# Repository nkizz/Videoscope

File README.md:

Board for viewing composite video (PAL, NTSC, or SECAM) on an oscilliscope
This is a layout of [this circuit by W2AEW](https://www.youtube.com/watch?v=yf4kOMSPbM0)

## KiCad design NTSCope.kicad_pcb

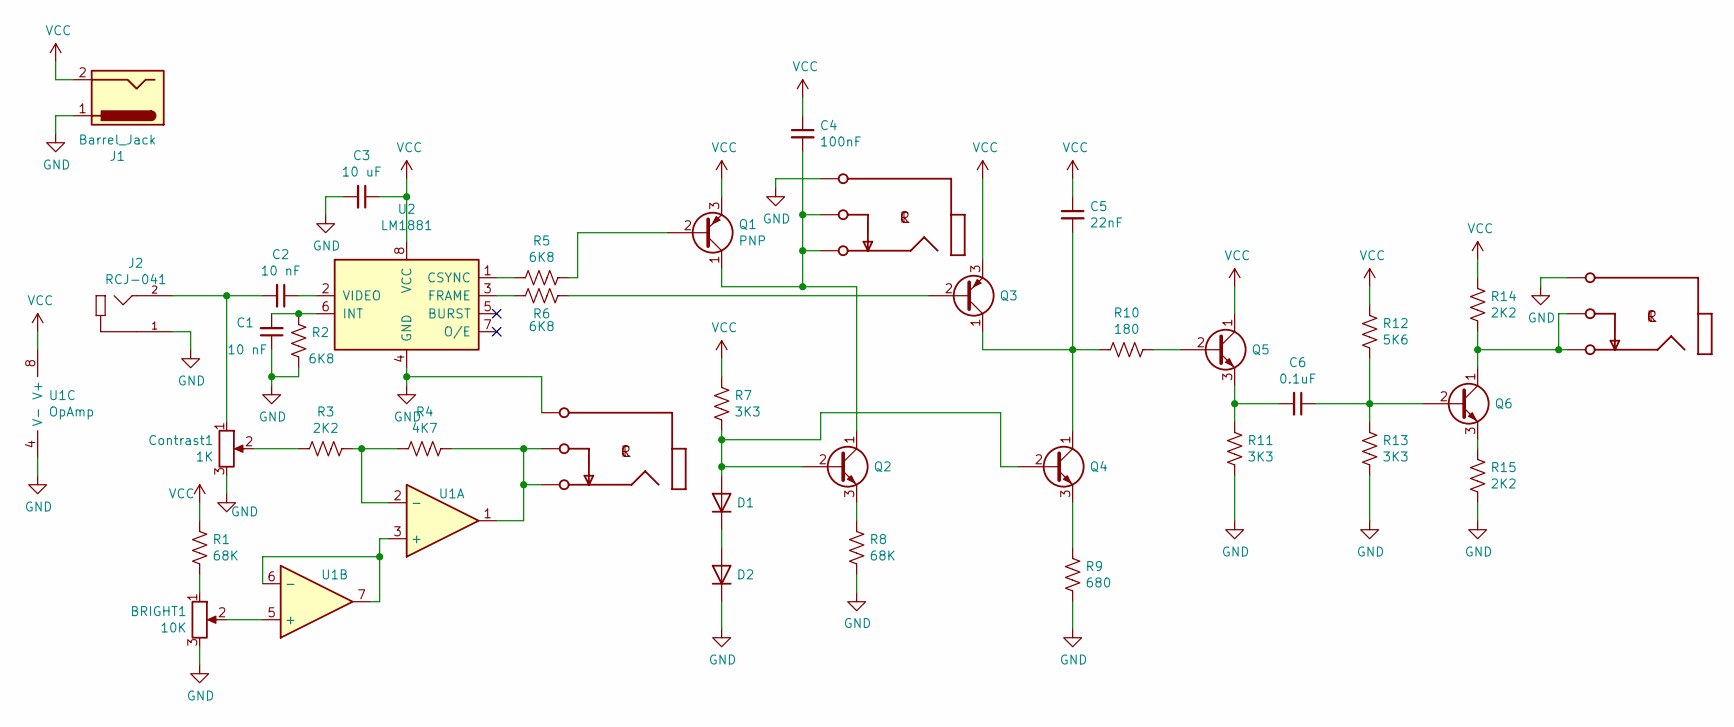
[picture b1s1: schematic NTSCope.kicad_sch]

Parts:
BRIGHT1: 10K; Potentiometer_Vishay_T73YP_Vertical
C1, C2: 10 nF; C_Disc_D5.0mm_W2.5mm_P2.50mm
C3: 10 uF; C_Disc_D5.0mm_W2.5mm_P2.50mm
C4: 100nF; C_Disc_D5.0mm_W2.5mm_P2.50mm
C5: 22nF; C_Disc_D5.0mm_W2.5mm_P2.50mm
C6: 0.1uF; C_Disc_D5.0mm_W2.5mm_P2.50mm
Contrast1: 1K; Potentiometer_Vishay_T73YP_Vertical
D1, D2: D; D_A-405_P7.62mm_Horizontal
J1: Barrel_Jack; BarrelJack_CUI_PJ-063AH_Horizontal_CircularHoles
J2: RCJ-041; CUI_RCJ-041
J3: PJRAN3X1U03X; PJRAN3X1U01X
Q1, Q3: PNP; TO-92_Inline_Wide
Q2, Q4, Q5, Q6: NPN; TO-92_Inline_Wide
R1, R8: 68K; R_Axial_DIN0207_L6.3mm_D2.5mm_P10.16mm_Horizontal
R2, R5, R6: 6K8; R_Axial_DIN0207_L6.3mm_D2.5mm_P10.16mm_Horizontal
R3, R14, R15: 2K2; R_Axial_DIN0207_L6.3mm_D2.5mm_P10.16mm_Horizontal
R4: 4K7; R_Axial_DIN0207_L6.3mm_D2.5mm_P10.16mm_Horizontal
R7, R11, R13: 3K3; R_Axial_DIN0207_L6.3mm_D2.5mm_P10.16mm_Horizontal
R9: 680; R_Axial_DIN0207_L6.3mm_D2.5mm_P10.16mm_Horizontal
R10: 180; R_Axial_DIN0207_L6.3mm_D2.5mm_P10.16mm_Horizontal
R12: 5K6; R_Axial_DIN0207_L6.3mm_D2.5mm_P10.16mm_Horizontal
U1: OpAmp; DIP-8_W7.62mm
U2: LM1881; DIP-8_W7.62mm

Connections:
GND: BRIGHT1.3, C1.1, C3.2, Contrast1.3, D2.1 (K), J1.1, J2.1, J3.1, J3.4, J3.7, R2.1, R8.2, R9.2, R11.2, R13.2, R15.2, U1.4 (V-), U2.4 (GND); also elsewhere on the board
unnamed 1: BRIGHT1.2, U1.5 (+); also elsewhere on the board
unnamed: C1.2, R2.2, U2.6 (INT)
unnamed: C2.1, U2.2 (VIDEO)
unnamed 4: C2.2, Contrast1.1, J2.2; also elsewhere on the board
unnamed: C4.2, J3.5, J3.6, Q1.1 (C), Q2.1 (C)
unnamed: C5.2, Q3.1 (C), Q4.1 (C), R10.2
unnamed: C6.1, Q6.2 (B), R12.2, R13.1
unnamed: C6.2, Q5.3 (E), R11.1
unnamed 9: Contrast1.2, R3.2; also elsewhere on the board
unnamed: D1.1 (K), D2.2 (A)
unnamed: D1.2 (A), Q2.2 (B), Q4.2 (B), R7.2
unnamed: J3.2, J3.3, R4.1, U1.1
unnamed: J3.8, J3.9, Q6.1 (C), R14.2
unnamed: Q1.2 (B), R5.1
unnamed: Q2.3 (E), R8.1
unnamed: Q3.2 (B), R6.1
unnamed: Q4.3 (E), R9.1
unnamed: Q5.2 (B), R10.1
unnamed: Q6.3 (E), R15.1
unnamed 20: BRIGHT1.1, R1.2; also elsewhere on the board
unnamed: R3.1, R4.2, U1.2 (-)
unnamed: R5.2, U2.1 (CSYNC)
unnamed: R6.2, U2.3 (FRAME)
unnamed: U1.3 (+), U1.6 (-), U1.7
VCC: C3.1, C4.1, C5.1, J1.2, Q1.3 (E), Q3.3 (E), Q5.1 (C), R1.1, R7.1, R12.1, R14.1, U1.8 (V+), U2.8 (VCC)

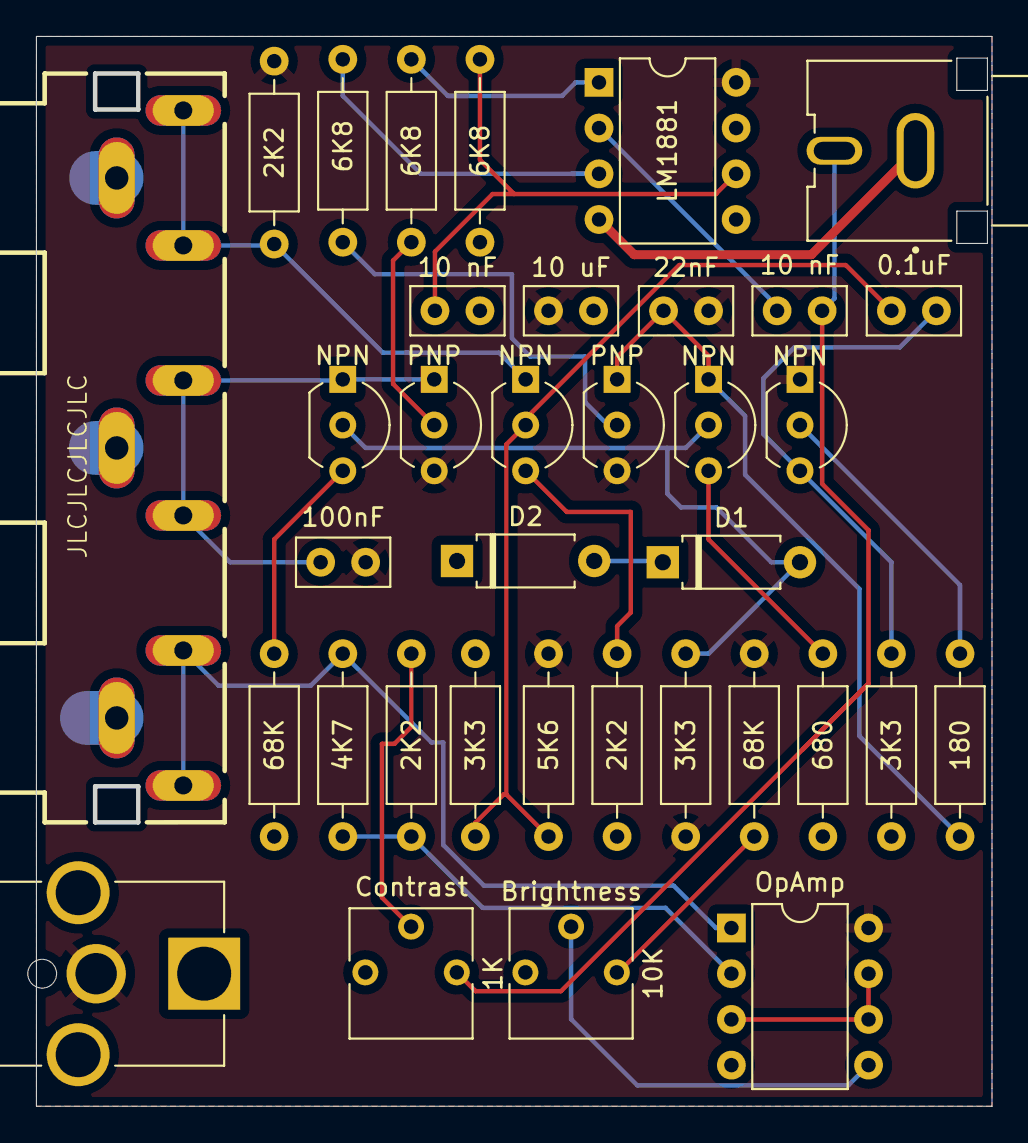
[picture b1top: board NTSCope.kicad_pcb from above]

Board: 2 copper layers, 52.9 x 59.2 mm, 36 parts (0 on the bottom side), 26 nets.

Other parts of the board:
Brightness: 10K; Potentiometer_Vishay_T73YP_Vertical
Contrast: 1K; Potentiometer_Vishay_T73YP_Vertical

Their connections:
GND: Brightness.3, Contrast.3; also elsewhere on the board
unnamed 1: Brightness.2; also elsewhere on the board
unnamed 4: Contrast.1; also elsewhere on the board
unnamed 9: Contrast.2; also elsewhere on the board
unnamed 20: Brightness.1; also elsewhere on the board

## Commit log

2021-04-03 Inital Commit - Has errors, use V2!
2021-05-03 Create testFile
